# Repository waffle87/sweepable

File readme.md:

# Sweepa**ble**

A wireless [Ferris Sweep](https://github.com/davidphilipbarr/Sweep) variant designed with integrated nRF52840 (Holyiot 18010).

## Compatibility

This PCB has the exact same dimensions and mounting points (via SplitKB Tenting Puck mount) as original Sweep PCB. However, it may not be compatible with all existing cases, as the microcontroller's antenna overhangs the board slightly, and the USB-C connectors are located on the inner side of the board, opposed to the top. This PCB only supports soldered Choc V1 switches, as it is common to build this keyboard without a plate.

## Ordering

The following instructions will be for [JLCPCB](https://jlcpcb.com), but should generally apply to most PCB manufacturers.

1. Upload the Gerber files from [production/gerbers.zip](production/gerbers.zip)
2. Set the following parameters: (and change other things like PCB quantity and colour as desired)

- **Different Design**: 2

3. For PCB assembly, choose **Economic** PCBA type and **Top Side** for assembly side.
4. Upload the [BOM](production/bom.csv) and [CPL](production/positions.csv) files.
5. Ensure the correct components have been selected, and all are in stock. An effort has been made to choose as few extended components as possible, but this is not possible for some.
6. Give a quick look at the component placement and make sure nothing looks too out of place. It is normal for some components to be shown oriented incorrectly or not quite where they belong. The PCB reviewers will usually correct this without issue.

### Additional components

For components to be installed by hand:
| Item | Quantity | Remarks |
|------|----------|---------|
| Holyiot 18010 Module ([Aliexpress](https://www.aliexpress.us/item/3256804605353119.html)) | 2 | Unfortunately not carried by JLCPCB. Easy enough to solder by hand. |
| 3.7v LiPo Battery | 2 | The batteries sold by [boardsource.xyz](https://boardsource.xyz/products/jst-ble) are compatible with the JST connectors used on this PCB. Otherwise, nearly any will do. |
| Choc v1 Switches | 34 | Must be soldered. |

## Build Instructions

These steps assume you already have an assembled PCB and are installing only microcontrollers and switches. If you are hand-assembling the PCBs with all components, the [interactive BOM](https://html-preview.github.io/?url=https://github.com/waffle87/sweepable/blob/master/ibom.html) will be helpful.

1. Install and solder microcontrollers with antenna facing upwards.
2. Flash bootloader to microcontrollers using an appropriate programmer connected to the SWD pads broken out on PCBs. For this, one can use the [Adafruit nRF52 bootloader](https://github.com/adafruit/Adafruit_nRF52_Bootloader) and a [Black Magic debugger](https://black-magic.org). Afterwards, firmware can be flashed over USB.
3. Install batteries appropriately. Battery terminals are labeled on the PCB with + and -. Some adhesive can be used to secure them to the PCB if desired. The small dot marker near the power switches denotes the **off** position.
4. Install switches, keycaps, and case.

## Firmware

ZMK Firmware support for this keyboard can be found [here](https://git.pngu.org/zmk_build/tree/sweepable).

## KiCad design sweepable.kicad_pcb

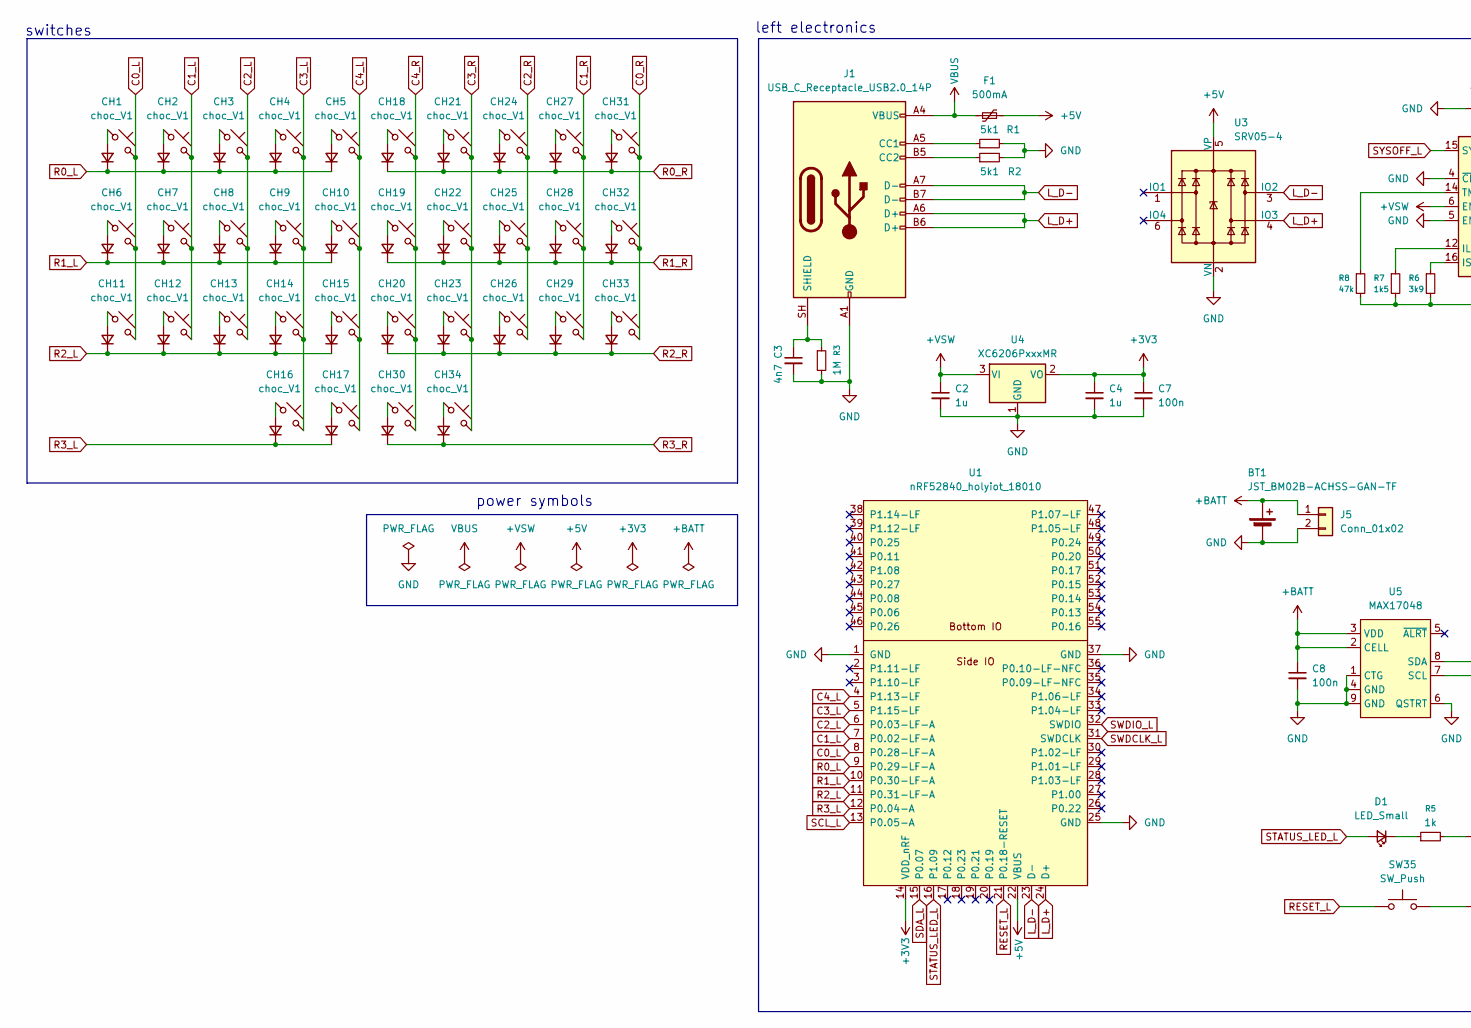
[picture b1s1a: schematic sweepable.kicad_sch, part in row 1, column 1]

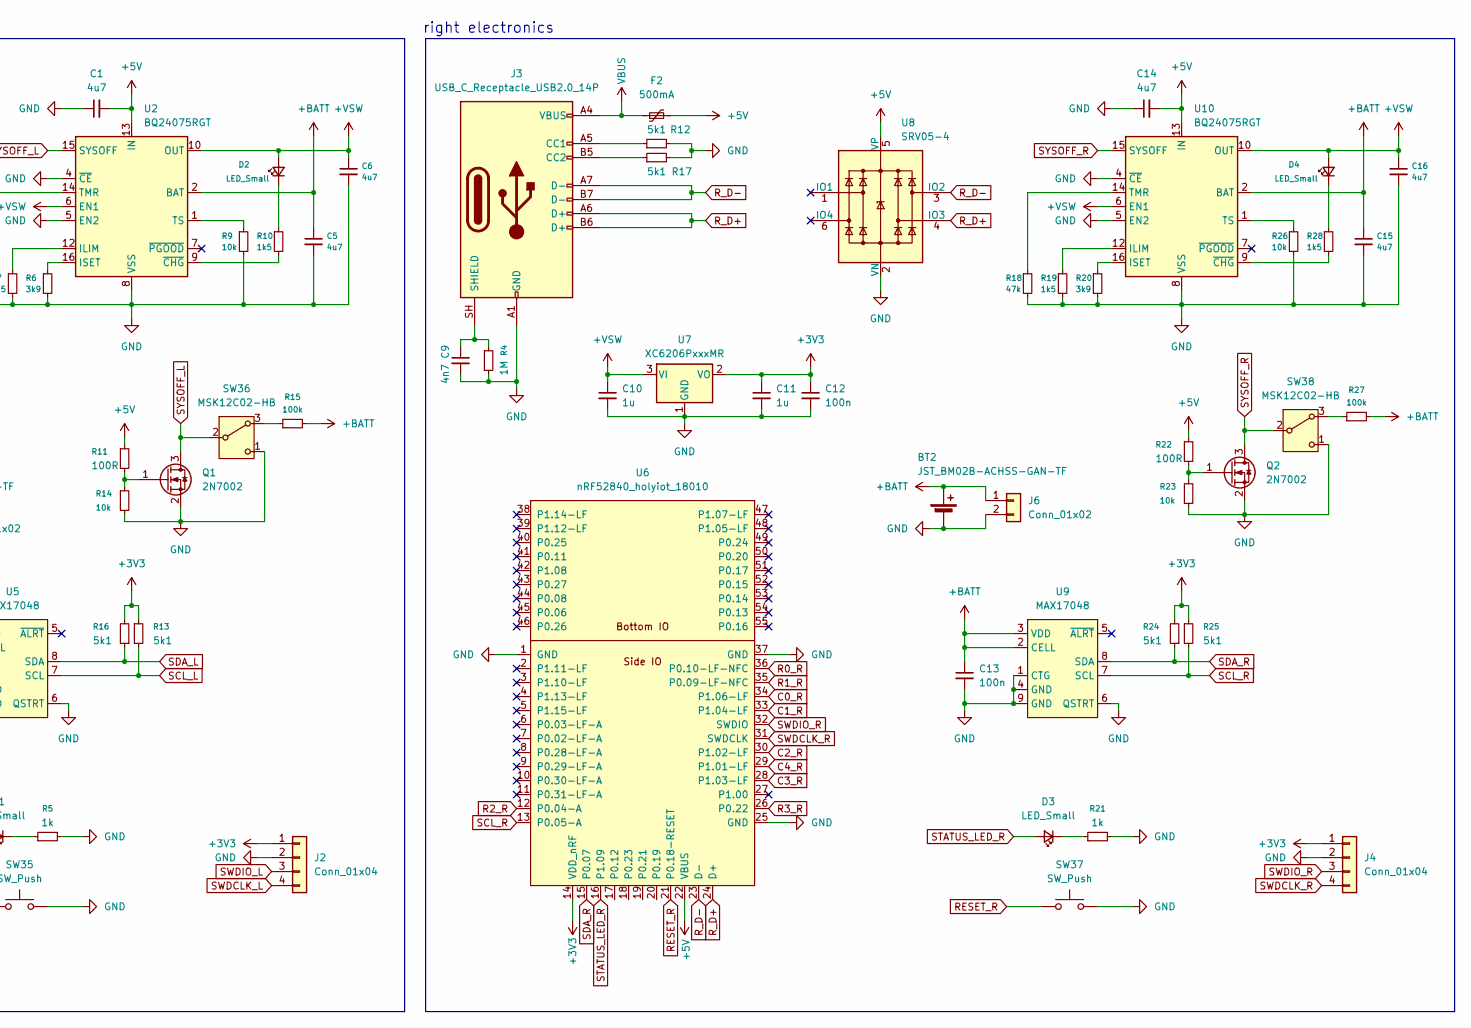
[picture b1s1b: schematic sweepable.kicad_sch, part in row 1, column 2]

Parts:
BT1, BT2: JST_BM02B-ACHSS-GAN-TF; CON_JST_ACH_BM02B
C1, C5, C6, C14, C15, C16: 4u7; C_0603_1608Metric
C2, C4, C10, C11: 1u; C_0603_1608Metric
C3, C9: 4n7; C_0603_1608Metric
C7, C8, C12, C13: 100n; C_0603_1608Metric
CH1, CH2, CH3, CH4, CH5, CH6, CH7, CH8, CH9, CH10, CH11, CH12, CH13, CH14, CH15, CH16, CH17, CH18, CH19, CH20, CH21, CH22, CH23, CH24, CH25, CH26, CH27, CH28, CH29, CH30, CH31, CH32, CH33, CH34: choc_V1; SW_choc_v1_1u
D1, D2, D3, D4: LED_Small; LED_0603_1608Metric
D5, D6, D7, D8, D9, D10, D11, D12, D13, D14, D15, D16, D17, D18, D19, D20, D21, D22, D23, D24, D25, D26, D27, D28, D29, D30, D31, D32, D33, D34, D35, D36, D37, D38: D_Small; D_SOD-323
F1, F2: 500mA; Fuse_1206_3216Metric
J1, J3: USB_C_Receptacle_USB2.0_14P; USB_C_Receptacle_HRO_TYPE-C-31-M-12
J2, J4: Conn_01x04; PinHeader_1x04_P2.54mm_Vertical
J5, J6: Conn_01x02; PinHeader_1x02_P1.27mm_Vertical
Q1, Q2: 2N7002; SOT-23
R1, R2, R12, R13, R16, R17, R24, R25: 5k1; R_0603_1608Metric
R3, R4: 1M; R_0603_1608Metric
R5, R21: 1k; R_0603_1608Metric
R6, R20: 3k9; R_0603_1608Metric
R7, R10, R19, R28: 1k5; R_0603_1608Metric
R8, R18: 47k; R_0603_1608Metric
R9, R14, R23, R26: 10k; R_0603_1608Metric
R11, R22: 100R; R_0603_1608Metric
R15, R27: 100k; R_0603_1608Metric
SW35, SW37: SW_Push; SW_SPST_TS-1088-xR020
SW36, SW38: MSK12C02-HB; SW_MSK12C02-HB
U1, U6: nRF52840_holyiot_18010
U2, U10: BQ24075RGT; VQFN-16-1EP_3x3mm_P0.5mm_EP1.6x1.6mm
U3, U8: SRV05-4; SOT-23-6-routable
U4, U7: XC6206PxxxMR; SOT-23-3
U5, U9: MAX17048; DFN-8-1EP_2x2mm_P0.5mm_EP0.9x1.3mm

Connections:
+3V3: C4.1, C7.1, C11.1, C12.1, J2.1, J4.1, R13.1, R16.2, R24.2, R25.1, U1.14 (VDD_nRF), U4.2 (VO), U6.14 (VDD_nRF), U7.2 (VO)
+5V: C1.2, C14.2, F1.2, F2.2, R11.1, R22.1, U1.22 (VBUS), U2.13 (IN), U3.5 (VP), U6.22 (VBUS), U8.5 (VP), U10.13 (IN)
+BATT: BT1.1 (+), BT2.1 (+), C5.1, C8.1, C13.1, C15.1, J5.1, J6.1, R15.2, R27.2, U2.2 (BAT), U2.3 (BAT), U5.2 (CELL), U5.3 (VDD), U9.2 (CELL), U9.3 (VDD), U10.2 (BAT), U10.3 (BAT)
+VSW: C2.1, C6.1, C10.1, C16.1, D2.2 (A), D4.2 (A), U2.6 (EN1), U2.10 (OUT), U2.11 (OUT), U4.3 (VI), U7.3 (VI), U10.6 (EN1), U10.10 (OUT), U10.11 (OUT)
C0_L: CH1.2, CH6.2, CH11.2, U1.8 (P0.28-LF-A)
C0_R: CH31.2, CH32.2, CH33.2, U6.34 (P1.06-LF)
C1_L: CH2.2, CH7.2, CH12.2, U1.7 (P0.02-LF-A)
C1_R: CH27.2, CH28.2, CH29.2, U6.33 (P1.04-LF)
C2_L: CH3.2, CH8.2, CH13.2, U1.6 (P0.03-LF-A)
C2_R: CH24.2, CH25.2, CH26.2, U6.30 (P1.02-LF)
C3_L: CH4.2, CH9.2, CH14.2, CH16.2, U1.5 (P1.15-LF)
C3_R: CH21.2, CH22.2, CH23.2, CH34.2, U6.28 (P1.03-LF)
C4_L: CH5.2, CH10.2, CH15.2, CH17.2, U1.4 (P1.13-LF)
C4_R: CH18.2, CH19.2, CH20.2, CH30.2, U6.29 (P1.01-LF)
GND: BT1.2 (-), BT2.2 (-), C1.1, C2.2, C3.2, C4.2, C5.2, C6.2, C7.2, C8.2, C9.2, C10.2, C11.2, C12.2, C13.2, C14.1, C15.2, C16.2, J1.A1 (GND), J1.A12 (GND), J1.B1 (GND), J1.B12 (GND), J2.2, J3.A1 (GND), J3.A12 (GND), J3.B1 (GND), J3.B12 (GND), J4.2, J5.2, J6.2, Q1.2 (S), Q2.2 (S), R1.2, R2.2, R3.2, R4.2, R5.2, R6.2, R7.2, R8.2, R9.2, R12.2, R14.2, R17.2, R18.2, R19.2, R20.2, R21.2, R23.2, R26.2, SW35.2, SW36.1 (C), SW37.2, SW38.1 (C), U1.1 (GND), U1.25 (GND), U1.37 (GND), U2.4 (~CE), U2.5 (EN2), U2.8 (VSS), U2.17 (VSS), U3.2 (VN), U4.1 (GND), U5.1 (CTG), U5.4 (GND), U5.6 (QSTRT), U5.9 (GND), U6.1 (GND), U6.25 (GND), U6.37 (GND), U7.1 (GND), U8.2 (VN), U9.1 (CTG), U9.4 (GND), U9.6 (QSTRT), U9.9 (GND), U10.4 (~CE), U10.5 (EN2), U10.8 (VSS), U10.17 (VSS)
L_D+: J1.A6 (D+), J1.B6 (D+), U1.24 (D+), U3.4 (IO3)
L_D-: J1.A7 (D-), J1.B7 (D-), U1.23 (D-), U3.3 (IO2)
unnamed: D1.1 (K), R5.1
unnamed: D2.1 (K), R10.1
unnamed: D3.1 (K), R21.1
unnamed: D4.1 (K), R28.1
unnamed: CH1.1, D5.2 (A)
unnamed: CH2.1, D6.2 (A)
unnamed: CH3.1, D7.2 (A)
unnamed: CH4.1, D8.2 (A)
unnamed: CH5.1, D9.2 (A)
unnamed: CH6.1, D10.2 (A)
unnamed: CH7.1, D11.2 (A)
unnamed: CH8.1, D12.2 (A)
unnamed: CH9.1, D13.2 (A)
unnamed: CH10.1, D14.2 (A)
unnamed: CH11.1, D15.2 (A)
unnamed: CH12.1, D16.2 (A)
unnamed: CH13.1, D17.2 (A)
unnamed: CH14.1, D18.2 (A)
unnamed: CH15.1, D19.2 (A)
unnamed: CH16.1, D20.2 (A)
unnamed: CH17.1, D21.2 (A)
unnamed: CH18.1, D22.2 (A)
unnamed: CH19.1, D23.2 (A)
unnamed: CH20.1, D24.2 (A)
unnamed: CH21.1, D25.2 (A)
unnamed: CH22.1, D26.2 (A)
unnamed: CH23.1, D27.2 (A)
unnamed: CH24.1, D28.2 (A)
unnamed: CH25.1, D29.2 (A)
unnamed: CH26.1, D30.2 (A)
unnamed: CH27.1, D31.2 (A)
unnamed: CH28.1, D32.2 (A)
unnamed: CH29.1, D33.2 (A)
unnamed: CH30.1, D34.2 (A)
unnamed: CH31.1, D35.2 (A)
unnamed: CH32.1, D36.2 (A)
unnamed: CH33.1, D37.2 (A)
unnamed: CH34.1, D38.2 (A)
unnamed: J1.A5 (CC1), R1.1
unnamed: J1.B5 (CC2), R2.1
unnamed: C3.1, J1.SH (SHIELD), R3.1
unnamed: J3.A5 (CC1), R12.1
unnamed: J3.B5 (CC2), R17.1
unnamed: C9.1, J3.SH (SHIELD), R4.1
unnamed: Q1.1 (G), R11.2, R14.1
unnamed: Q2.1 (G), R22.2, R23.1
unnamed: R15.1, SW36.3 (A)
unnamed: R27.1, SW38.3 (A)
unnamed: R7.1, U2.12 (ILIM)
unnamed: R6.1, U2.16 (ISET)
unnamed: R8.1, U2.14 (TMR)
unnamed: R9.1, U2.1 (TS)
unnamed: R10.2, U2.9 (~CHG)
unnamed: R19.1, U10.12 (ILIM)
unnamed: R20.1, U10.16 (ISET)
unnamed: R18.1, U10.14 (TMR)
unnamed: R26.1, U10.1 (TS)
unnamed: R28.2, U10.9 (~CHG)
R0_L: D5.1 (K), D6.1 (K), D7.1 (K), D8.1 (K), D9.1 (K), U1.9 (P0.29-LF-A)
R0_R: D22.1 (K), D25.1 (K), D28.1 (K), D31.1 (K), D35.1 (K), U6.36 (P0.10-LF-NFC)
R1_L: D10.1 (K), D11.1 (K), D12.1 (K), D13.1 (K), D14.1 (K), U1.10 (P0.30-LF-A)
R1_R: D23.1 (K), D26.1 (K), D29.1 (K), D32.1 (K), D36.1 (K), U6.35 (P0.09-LF-NFC)
R2_L: D15.1 (K), D16.1 (K), D17.1 (K), D18.1 (K), D19.1 (K), U1.11 (P0.31-LF-A)
R2_R: D24.1 (K), D27.1 (K), D30.1 (K), D33.1 (K), D37.1 (K), U6.12 (P0.04-A)
R3_L: D20.1 (K), D21.1 (K), U1.12 (P0.04-A)
R3_R: D34.1 (K), D38.1 (K), U6.26 (P0.22)
RESET_L: SW35.1, U1.21 (P0.18-RESET)
RESET_R: SW37.1, U6.21 (P0.18-RESET)
R_D+: J3.A6 (D+), J3.B6 (D+), U6.24 (D+), U8.4 (IO3)
R_D-: J3.A7 (D-), J3.B7 (D-), U6.23 (D-), U8.3 (IO2)
SCL_L: R13.2, U1.13 (P0.05-A), U5.7 (SCL)
SCL_R: R25.2, U6.13 (P0.05-A), U9.7 (SCL)
SDA_L: R16.1, U1.15 (P0.07), U5.8 (SDA)
SDA_R: R24.1, U6.15 (P0.07), U9.8 (SDA)
STATUS_LED_L: D1.2 (A), U1.16 (P1.09)
STATUS_LED_R: D3.2 (A), U6.16 (P1.09)
SWDCLK_L: J2.4, U1.31 (SWDCLK)
SWDCLK_R: J4.4, U6.31 (SWDCLK)
SWDIO_L: J2.3, U1.32 (SWDIO)
SWDIO_R: J4.3, U6.32 (SWDIO)
SYSOFF_L: Q1.3 (D), SW36.2 (B), U2.15 (SYSOFF)
SYSOFF_R: Q2.3 (D), SW38.2 (B), U10.15 (SYSOFF)
VBUS: F1.1, F2.1, J1.A4 (VBUS), J1.A9 (VBUS), J1.B4 (VBUS), J1.B9 (VBUS), J3.A4 (VBUS), J3.A9 (VBUS), J3.B4 (VBUS), J3.B9 (VBUS)

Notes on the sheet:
right electronics
switches
left electronics
power symbols

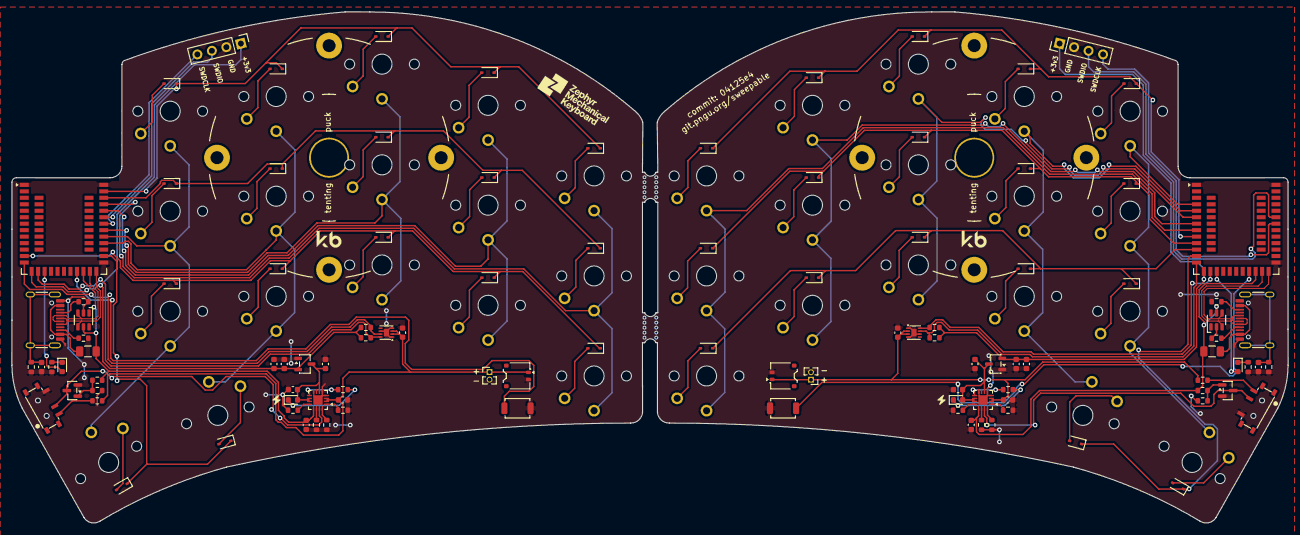
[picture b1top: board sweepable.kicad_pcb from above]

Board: 2 copper layers, 216.9 x 86.9 mm, 142 parts (0 on the bottom side), 100 nets.

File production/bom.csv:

Designator,Footprint,Quantity,Value,LCSC Part #
"BT1, BT2",CON_JST_ACH_BM02B,2,Battery_Cell,C265007
"C1, C14, C15, C16, C5, C6",0603,6,4u7,C19666
"C10, C11, C2, C4",0603,4,1u,C15849
"C12, C13, C7, C8",0603,4,100n,C14663
"C3, C9",0603,2,4n7,C53987
"D1, D2, D3, D4",0603,2,LED_Small,C2286
"D10, D11, D12, D13, D14, D15, D16, D17, D18, D19, D20, D21, D22, D23, D24, D25, D26, D27, D28, D29, D30, D31, D32, D33, D34, D35, D36, D37, D38, D5, D6, D7, D8, D9",D_SOD-323,34,D_Small,C2128
"F1, F2",1206,2,500mA,C70070
"J1, J3",USB_C_Receptacle_HRO_TYPE-C-31-M-12,2,USB_C_Receptacle_USB2.0_14P,C165948
"Q1, Q2",SOT-23,2,2N7002,C8545
"R1, R12, R13, R16, R17, R2, R24, R25",0603,8,5k1,C23186
"R10, R19, R28, R7",0603,4,1k5,C22843
"R11, R22",0603,2,100R,C22775
"R14, R23, R26, R9",0603,4,10k,C25804
"R15, R27",0603,2,100k,C25803
"R18, R8",0603,2,47k,C25819
"R20, R6",0603,2,3k9,C23018
"R21, R5",0603,2,1k,C21190
"R3, R4",0603,2,1M,C22935
"SW35, SW37",SW_SPST_TS-1088-xR020,2,SW_Push,C720477
"SW36, SW38",SW_MSK12C02-HB,2,SW_SPDT_321,C431541
"U10, U2",VQFN-16-1EP_3x3mm_P0.5mm_EP1.6x1.6mm,2,BQ24075RGT,C15464
"U3, U8",SOT-23-6-routable,2,SRV05-4,C558418
"U4, U7",SOT-23-3,2,XC6206PxxxMR,C5446
"U5, U9",DFN-8-1EP_2x2mm_P0.5mm_EP0.9x1.3mm,2,MAX17048,C2682616

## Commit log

2026-05-16 Adds PCBs and production files
2026-05-17 Update silkscreen graphics & SVG images, and correct BOM part number
2026-05-17 Correct to JLCPCB basic part number
2026-05-21 Add readme, improve some traces

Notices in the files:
sweepable.kicad_pcb:
Solderpad Hardware License v2.1
